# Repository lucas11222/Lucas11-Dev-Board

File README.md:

# Lucas11-Dev-Board

## An fast Dev Board for the XIAO RP2350 for prototyping and just making projects without soldering every time.
## But why?
Becuse this is a dream that i have a few months before Highway so now that Highway is happening is the perfect moment to start making this dream true.
## But how it works?
Its a board with MX switches, OLED screen, MINI-E leds, and all-in-one using the power of the XIAO RP2350.
## How to use?  
First install the SSD1406 module with this
```
cd example_firmware
cd lib
mpremote mip install ./ssd1306.py
```
Then use the example_firmware to start programing in the board.

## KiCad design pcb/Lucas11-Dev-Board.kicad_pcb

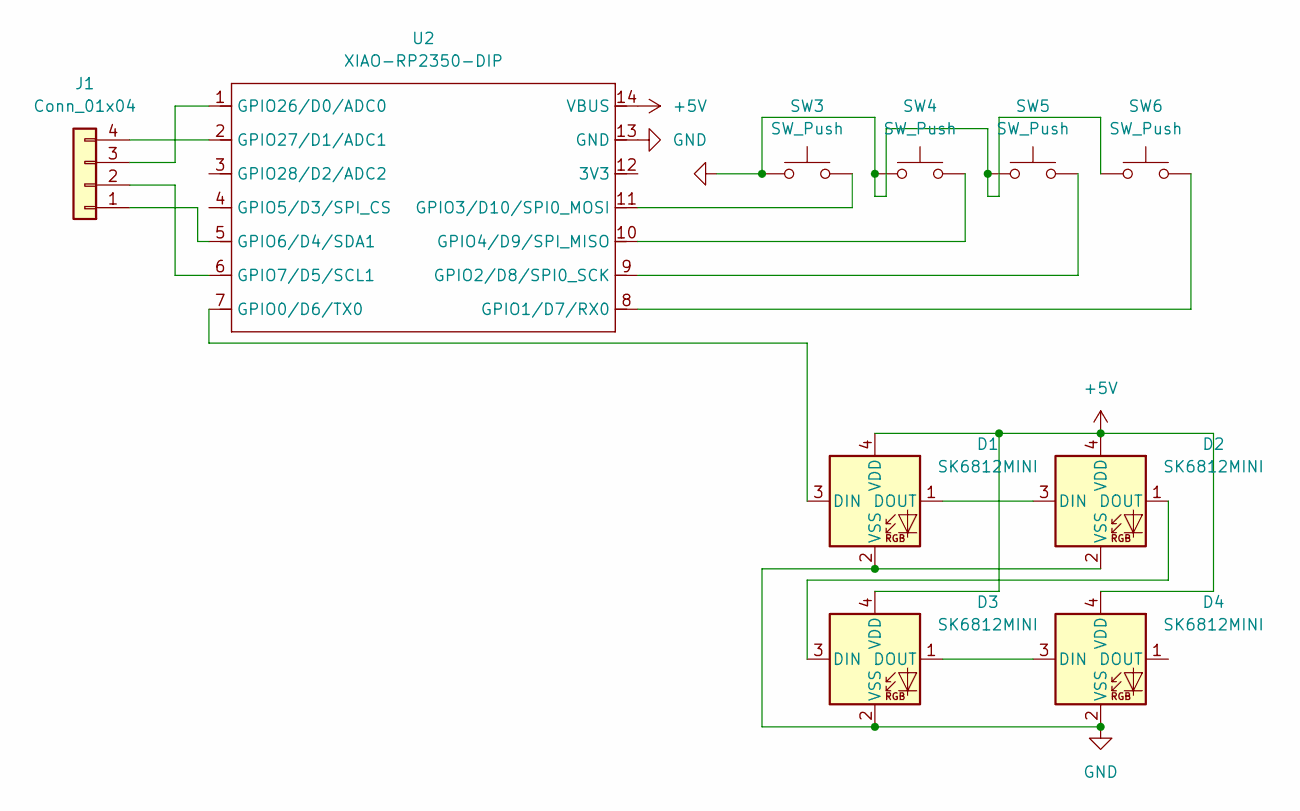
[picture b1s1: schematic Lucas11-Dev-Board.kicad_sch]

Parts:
D1, D2, D3, D4: SK6812MINI; LED_SK6812MINI_PLCC4_3.5x3.5mm_P1.75mm
J1: Conn_01x04; SSD1306-0.91-OLED-4pin-128x32
SW3, SW4, SW5, SW6: SW_Push; SW_Cherry_MX_1.00u_PCB
U2: XIAO-RP2350-DIP

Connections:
+5V: D1.4 (VDD), D2.4 (VDD), D3.4 (VDD), D4.4 (VDD), U2.14 (VBUS)
GND: D1.2 (VSS), D2.2 (VSS), D3.2 (VSS), D4.2 (VSS), SW3.1, SW4.1, SW5.1, SW6.1, U2.13 (GND)
unnamed: D1.3 (DIN), U2.7 (GPIO0/D6/TX0)
unnamed: D1.1 (DOUT), D2.3 (DIN)
unnamed: D2.1 (DOUT), D3.3 (DIN)
unnamed: D3.1 (DOUT), D4.3 (DIN)
unnamed: J1.1, U2.5 (GPIO6/D4/SDA1)
unnamed: J1.2, U2.6 (GPIO7/D5/SCL1)
unnamed: J1.3, U2.1 (GPIO26/D0/ADC0)
unnamed: J1.4, U2.2 (GPIO27/D1/ADC1)
unnamed: SW6.2, U2.8 (GPIO1/D7/RX0)
unnamed: SW5.2, U2.9 (GPIO2/D8/SPI0_SCK)
unnamed: SW3.2, U2.11 (GPIO3/D10/SPI0_MOSI)
unnamed: SW4.2, U2.10 (GPIO4/D9/SPI_MISO)

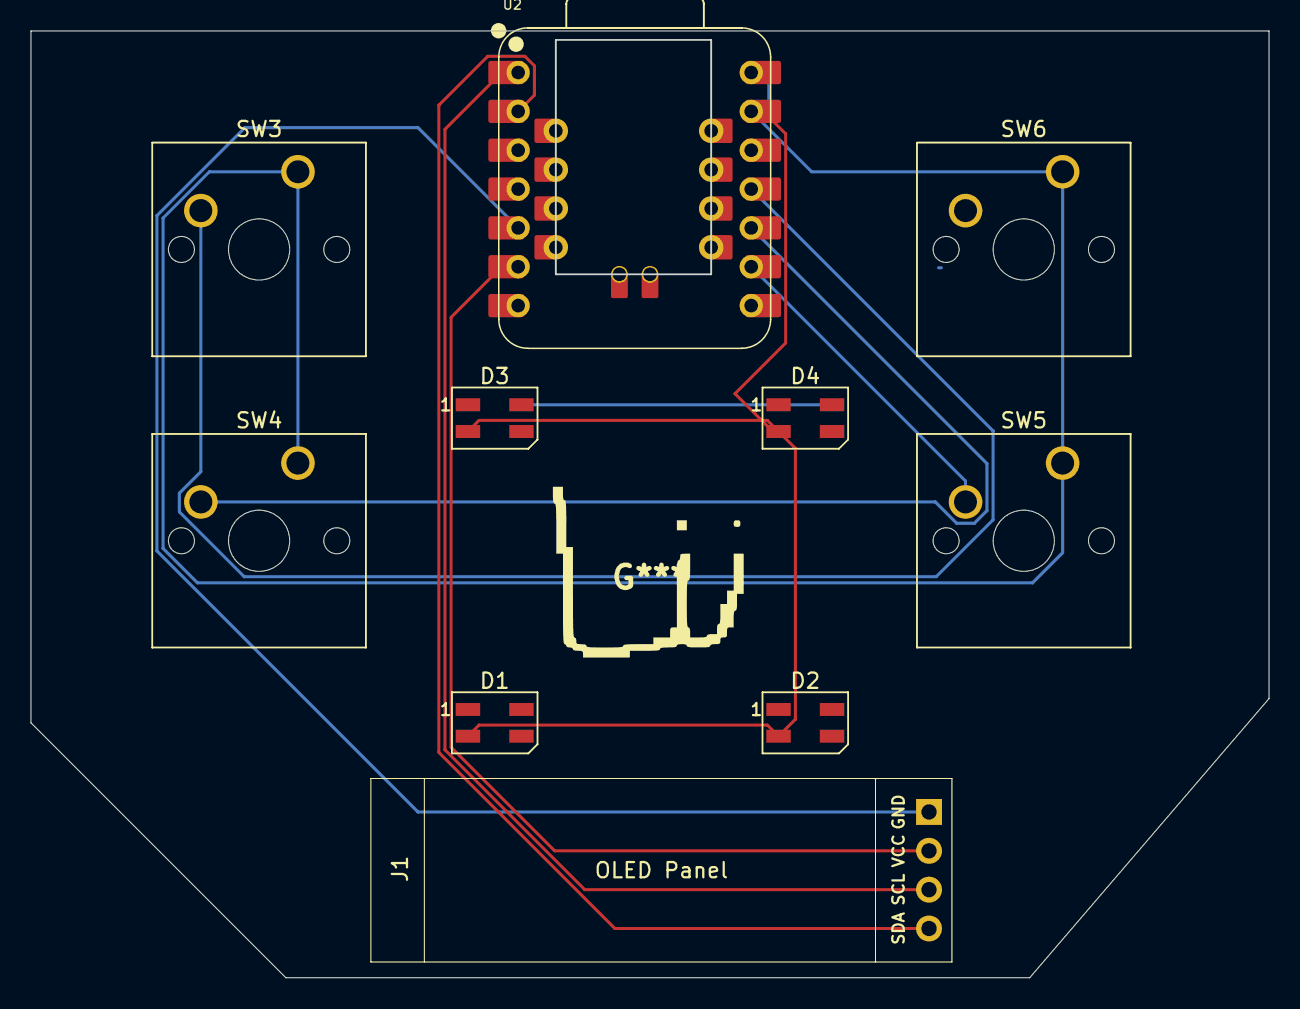
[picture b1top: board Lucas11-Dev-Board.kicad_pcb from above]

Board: 2 copper layers, 80.9 x 61.8 mm, 10 parts (0 on the bottom side), 14 nets.

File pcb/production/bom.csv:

Designator,Footprint,Quantity,Value,LCSC Part #
"D1, D2, D3, D4",LED_SK6812MINI_PLCC4_3.5x3.5mm_P1.75mm,4,SK6812MINI,
J1,SSD1306-0.91-OLED-4pin-128x32,1,Conn_01x04,
"SW3, SW4, SW5, SW6",SW_Cherry_MX_1.00u_PCB,4,SW_Push,
U1,XIAO-RP2350-SMD,1,XIAO-RP2350-SMD,

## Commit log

2025-05-24 Added the README
2025-05-24 Added Leds and keys and finished the pcb part.
2025-05-24 Logo wasent centered XD
2025-05-24 Finished the PCB!!!!
2025-05-24 Fix all the DRC errors
2025-05-24 Added the OLED screen to the example firmware
